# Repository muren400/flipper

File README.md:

# flipper
Currently flipper is just a flip dot clock. display.h could be used for all kinds of flip dot applications though.

## Hardware
Make sure to import https://github.com/espressif/kicad-libraries/ to open the kicad project

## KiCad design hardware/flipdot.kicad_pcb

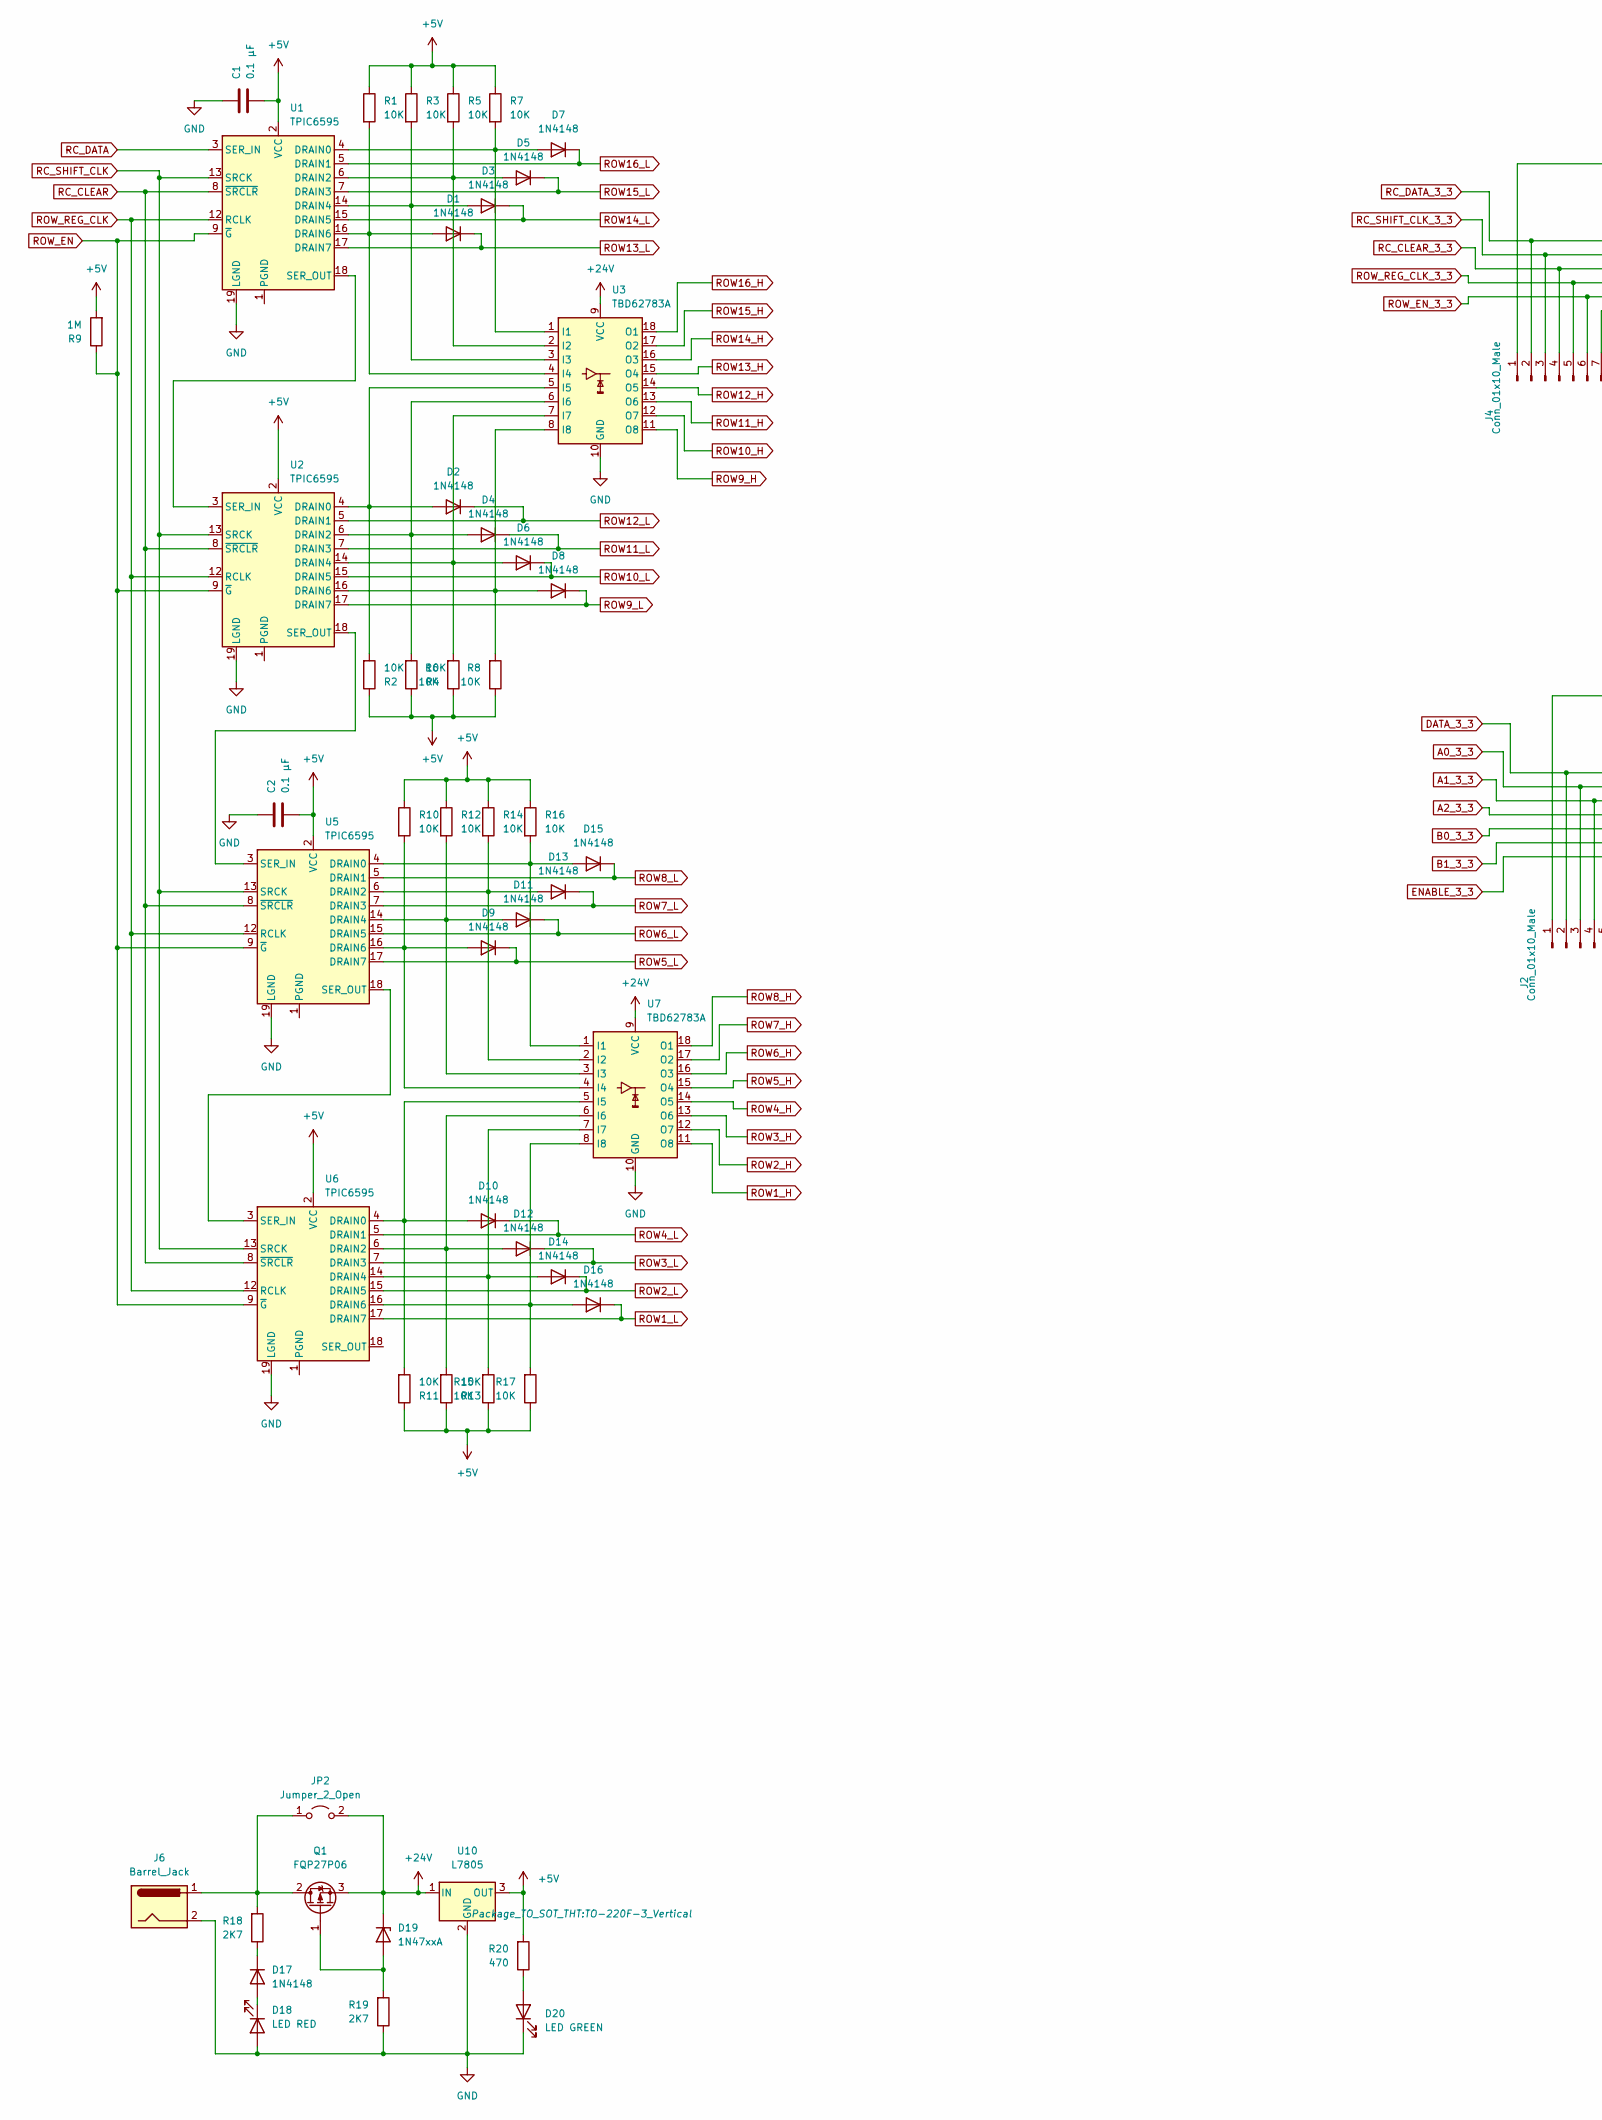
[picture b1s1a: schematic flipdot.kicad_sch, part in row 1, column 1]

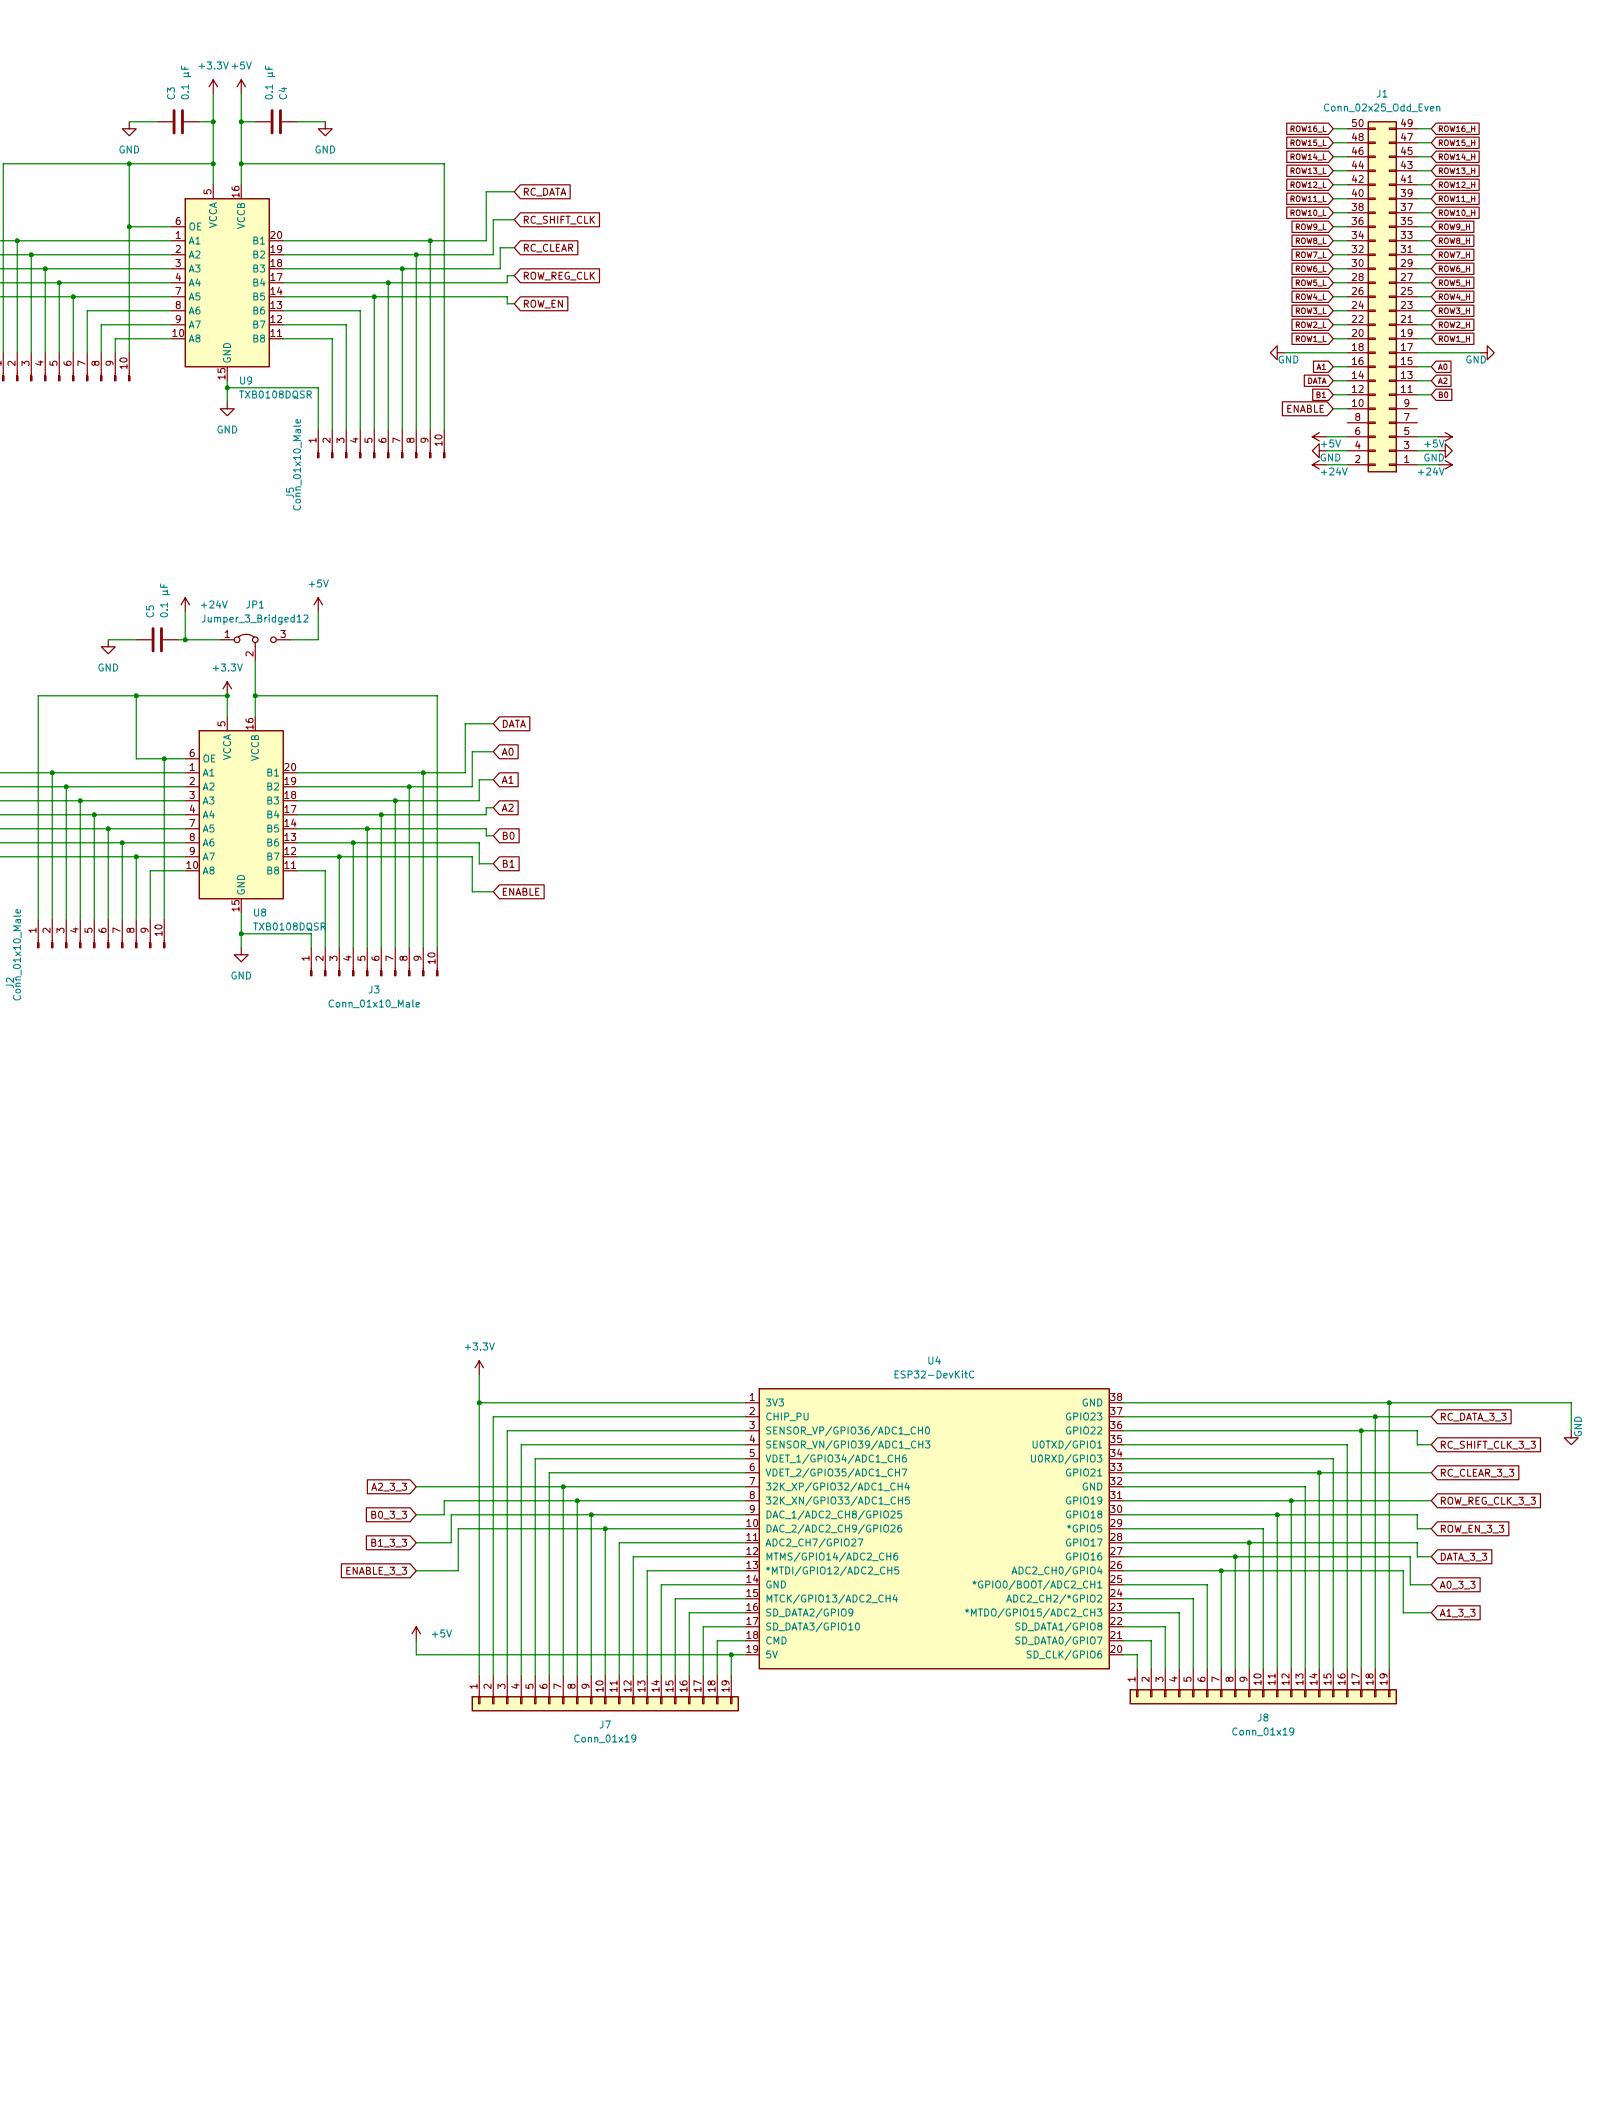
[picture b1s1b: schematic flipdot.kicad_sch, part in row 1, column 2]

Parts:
C1, C2, C3, C4, C5: 0.1 µF; C_Rect_L7.2mm_W2.5mm_P5.00mm_FKS2_FKP2_MKS2_MKP2
D1, D2, D3, D4, D5, D6, D7, D8, D9, D10, D11, D12, D13, D14, D15, D16, D17: 1N4148; D_DO-35_SOD27_P7.62mm_Horizontal
D18: LED RED; LED_D3.0mm
D19: 1N47xxA; D_DO-41_SOD81_P10.16mm_Horizontal
D20: LED GREEN; LED_D3.0mm
J1: Conn_02x25_Odd_Even; PinSocket_2x25_P2.54mm_Vertical
J2, J3, J4, J5: Conn_01x10_Male; PinSocket_1x10_P2.54mm_Vertical
J6: Barrel_Jack; BarrelJack_CUI_PJ-063AH_Horizontal
J7, J8: Conn_01x19; PinHeader_1x19_P2.54mm_Vertical
JP1: Jumper_3_Bridged12; PinHeader_1x03_P2.54mm_Vertical
JP2: Jumper_2_Open; PinHeader_1x02_P2.54mm_Vertical
Q1: FQP27P06; TO-220-3_Vertical
R1, R2, R3, R4, R5, R6, R7, R8, R10, R11, R12, R13, R14, R15, R16, R17: 10K; R_Axial_DIN0204_L3.6mm_D1.6mm_P7.62mm_Horizontal
R9: 1M; R_Axial_DIN0204_L3.6mm_D1.6mm_P7.62mm_Horizontal
R18, R19: 2K7; R_Axial_DIN0204_L3.6mm_D1.6mm_P7.62mm_Horizontal
R20: 470; R_Axial_DIN0204_L3.6mm_D1.6mm_P7.62mm_Horizontal
U1, U2, U5, U6: TPIC6595; DIP-20_W7.62mm_Socket_LongPads
U3, U7: TBD62783A; DIP-18_W7.62mm_Socket_LongPads
U4: ESP32-DevKitC
U8, U9: TXB0108DQSR; USON-20_2x4mm_P0.4mm
U10: L7805; TO-220F-3_Vertical

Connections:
+3.3V: C3.2, J2.1, J2.10, J4.1, J4.10, J7.1, U4.1 (3V3), U8.5 (VCCA), U8.6 (OE), U9.5 (VCCA), U9.6 (OE)
+5V: C1.2, C2.2, C4.2, J1.5, J1.6, J5.10, J7.19, JP1.3 (B), R1.1, R2.1, R3.1, R4.1, R5.1, R6.1, R7.1, R8.1, R9.2, R10.1, R11.1, R12.1, R13.1, R14.1, R15.1, R16.1, R17.1, R20.2, U1.2 (VCC), U2.2 (VCC), U4.19 (5V), U5.2 (VCC), U6.2 (VCC), U9.16 (VCCB), U10.3 (OUT)
+24V: C5.2, D19.1 (K), J1.1, J1.2, JP1.1 (A), JP2.2 (B), Q1.3 (S), U3.9 (VCC), U7.9 (VCC), U10.1 (IN)
A0: J1.15, J3.8, U8.19 (B2)
A0_3_3: J2.3, J8.8, U4.27 (GPIO16), U8.2 (A2)
A1: J1.16, J3.7, U8.18 (B3)
A1_3_3: J2.4, J8.7, U4.26 (ADC2_CH0/GPIO4), U8.3 (A3)
A2: J1.13, J3.6, U8.17 (B4)
A2_3_3: J2.5, J7.7, U4.7 (32K_XP/GPIO32/ADC1_CH4), U8.4 (A4)
B0: J1.11, J3.5, U8.14 (B5)
B0_3_3: J2.6, J7.8, U4.8 (32K_XN/GPIO33/ADC1_CH5), U8.7 (A5)
B1: J1.12, J3.4, U8.13 (B6)
B1_3_3: J2.7, J7.9, U4.9 (DAC_1/ADC2_CH8/GPIO25), U8.8 (A6)
DATA: J1.14, J3.9, U8.20 (B1)
DATA_3_3: J2.2, J8.9, U4.28 (GPIO17), U8.1 (A1)
ENABLE: J1.10, J3.3, U8.12 (B7)
ENABLE_3_3: J2.8, J7.10, U4.10 (DAC_2/ADC2_CH9/GPIO26), U8.9 (A7)
GND: C1.1, C2.1, C3.1, C4.1, C5.1, D18.2 (A), D20.1 (K), J1.3, J1.4, J1.17, J1.18, J3.1, J5.1, J6.2, J8.19, R19.1, U1.19 (LGND), U2.19 (LGND), U3.10 (GND), U4.38 (GND), U5.19 (LGND), U6.19 (LGND), U7.10 (GND), U8.15 (GND), U9.15 (GND), U10.2 (GND)
unnamed: D1.2 (A), R1.2, U1.16 (DRAIN6), U3.4 (I4)
unnamed: D2.2 (A), R2.2, U2.4 (DRAIN0), U3.5 (I5)
unnamed: D3.2 (A), R3.2, U1.14 (DRAIN4), U3.3 (I3)
unnamed: D4.2 (A), R4.2, U2.6 (DRAIN2), U3.6 (I6)
unnamed: D5.2 (A), R5.2, U1.6 (DRAIN2), U3.2 (I2)
unnamed: D6.2 (A), R6.2, U2.14 (DRAIN4), U3.7 (I7)
unnamed: D7.2 (A), R7.2, U1.4 (DRAIN0), U3.1 (I1)
unnamed: D8.2 (A), R8.2, U2.16 (DRAIN6), U3.8 (I8)
unnamed: D9.2 (A), R10.2, U5.16 (DRAIN6), U7.4 (I4)
unnamed: D10.2 (A), R11.2, U6.4 (DRAIN0), U7.5 (I5)
unnamed: D11.2 (A), R12.2, U5.14 (DRAIN4), U7.3 (I3)
unnamed: D12.2 (A), R13.2, U6.6 (DRAIN2), U7.6 (I6)
unnamed: D13.2 (A), R14.2, U5.6 (DRAIN2), U7.2 (I2)
unnamed: D14.2 (A), R15.2, U6.14 (DRAIN4), U7.7 (I7)
unnamed: D15.2 (A), R16.2, U5.4 (DRAIN0), U7.1 (I1)
unnamed: D16.2 (A), R17.2, U6.16 (DRAIN6), U7.8 (I8)
unnamed: D17.2 (A), D18.1 (K)
unnamed: D17.1 (K), R18.1
unnamed: D19.2 (A), Q1.1 (G), R19.2
unnamed: D20.2 (A), R20.1
unnamed: J2.9, U8.10 (A8)
unnamed: J3.2, U8.11 (B8)
unnamed: J3.10, JP1.2 (C), U8.16 (VCCB)
unnamed: J4.7, U9.8 (A6)
unnamed: J4.8, U9.9 (A7)
unnamed: J4.9, U9.10 (A8)
unnamed: J5.2, U9.11 (B8)
unnamed: J5.3, U9.12 (B7)
unnamed: J5.4, U9.13 (B6)
unnamed: J7.2, U4.2 (CHIP_PU)
unnamed: J7.3, U4.3 (SENSOR_VP/GPIO36/ADC1_CH0)
unnamed: J7.4, U4.4 (SENSOR_VN/GPIO39/ADC1_CH3)
unnamed: J7.5, U4.5 (VDET_1/GPIO34/ADC1_CH6)
unnamed: J7.6, U4.6 (VDET_2/GPIO35/ADC1_CH7)
unnamed: J7.11, U4.11 (ADC2_CH7/GPIO27)
unnamed: J7.12, U4.12 (MTMS/GPIO14/ADC2_CH6)
unnamed: J7.13, U4.13 (*MTDI/GPIO12/ADC2_CH5)
unnamed: J7.14, U4.14 (GND)
unnamed: J7.15, U4.15 (MTCK/GPIO13/ADC2_CH4)
unnamed: J7.16, U4.16 (SD_DATA2/GPIO9)
unnamed: J7.17, U4.17 (SD_DATA3/GPIO10)
unnamed: J7.18, U4.18 (CMD)
unnamed: J8.1, U4.20 (SD_CLK/GPIO6)
unnamed: J8.2, U4.21 (SD_DATA0/GPIO7)
unnamed: J8.3, U4.22 (SD_DATA1/GPIO8)
unnamed: J8.4, U4.23 (*MTDO/GPIO15/ADC2_CH3)
unnamed: J8.5, U4.24 (ADC2_CH2/*GPIO2)
unnamed: J8.6, U4.25 (*GPIO0/BOOT/ADC2_CH1)
unnamed: J8.10, U4.29 (*GPIO5)
unnamed: J8.13, U4.32 (GND)
unnamed: J8.15, U4.34 (U0RXD/GPIO3)
unnamed: J8.16, U4.35 (U0TXD/GPIO1)
unnamed: J6.1, JP2.1 (A), Q1.2 (D), R18.2
unnamed: U1.1 (PGND), U1.10 (PGND), U1.11 (PGND), U1.20 (PGND)
unnamed: U1.18 (SER_OUT), U2.3 (SER_IN)
unnamed: U2.1 (PGND), U2.10 (PGND), U2.11 (PGND), U2.20 (PGND)
unnamed: U2.18 (SER_OUT), U5.3 (SER_IN)
unnamed: U5.1 (PGND), U5.10 (PGND), U5.11 (PGND), U5.20 (PGND)
unnamed: U5.18 (SER_OUT), U6.3 (SER_IN)
unnamed: U6.1 (PGND), U6.10 (PGND), U6.11 (PGND), U6.20 (PGND)
RC_CLEAR: J5.7, U1.8 (~SRCLR), U2.8 (~SRCLR), U5.8 (~SRCLR), U6.8 (~SRCLR), U9.18 (B3)
RC_CLEAR_3_3: J4.4, J8.14, U4.33 (GPIO21), U9.3 (A3)
RC_DATA: J5.9, U1.3 (SER_IN), U9.20 (B1)
RC_DATA_3_3: J4.2, J8.18, U4.37 (GPIO23), U9.1 (A1)
RC_SHIFT_CLK: J5.8, U1.13 (SRCK), U2.13 (SRCK), U5.13 (SRCK), U6.13 (SRCK), U9.19 (B2)
RC_SHIFT_CLK_3_3: J4.3, J8.17, U4.36 (GPIO22), U9.2 (A2)
ROW1_H: J1.19, U7.11 (O8)
ROW1_L: D16.1 (K), J1.20, U6.17 (DRAIN7)
ROW2_H: J1.21, U7.12 (O7)
ROW2_L: D14.1 (K), J1.22, U6.15 (DRAIN5)
ROW3_H: J1.23, U7.13 (O6)
ROW3_L: D12.1 (K), J1.24, U6.7 (DRAIN3)
ROW4_H: J1.25, U7.14 (O5)
ROW4_L: D10.1 (K), J1.26, U6.5 (DRAIN1)
ROW5_H: J1.27, U7.15 (O4)
ROW5_L: D9.1 (K), J1.28, U5.17 (DRAIN7)
ROW6_H: J1.29, U7.16 (O3)
ROW6_L: D11.1 (K), J1.30, U5.15 (DRAIN5)
ROW7_H: J1.31, U7.17 (O2)
ROW7_L: D13.1 (K), J1.32, U5.7 (DRAIN3)
ROW8_H: J1.33, U7.18 (O1)
ROW8_L: D15.1 (K), J1.34, U5.5 (DRAIN1)
ROW9_H: J1.35, U3.11 (O8)
ROW9_L: D8.1 (K), J1.36, U2.17 (DRAIN7)
ROW10_H: J1.37, U3.12 (O7)
ROW10_L: D6.1 (K), J1.38, U2.15 (DRAIN5)
ROW11_H: J1.39, U3.13 (O6)
ROW11_L: D4.1 (K), J1.40, U2.7 (DRAIN3)
ROW12_H: J1.41, U3.14 (O5)
ROW12_L: D2.1 (K), J1.42, U2.5 (DRAIN1)
ROW13_H: J1.43, U3.15 (O4)
ROW13_L: D1.1 (K), J1.44, U1.17 (DRAIN7)
ROW14_H: J1.45, U3.16 (O3)
ROW14_L: D3.1 (K), J1.46, U1.15 (DRAIN5)
ROW15_H: J1.47, U3.17 (O2)
ROW15_L: D5.1 (K), J1.48, U1.7 (DRAIN3)
ROW16_H: J1.49, U3.18 (O1)
ROW16_L: D7.1 (K), J1.50, U1.5 (DRAIN1)
ROW_EN: J5.5, R9.1, U1.9 (~G), U2.9 (~G), U5.9 (~G), U6.9 (~G), U9.14 (B5)
ROW_EN_3_3: J4.6, J8.11, U4.30 (GPIO18), U9.7 (A5)
ROW_REG_CLK: J5.6, U1.12 (RCLK), U2.12 (RCLK), U5.12 (RCLK), U6.12 (RCLK), U9.17 (B4)
ROW_REG_CLK_3_3: J4.5, J8.12, U4.31 (GPIO19), U9.4 (A4)

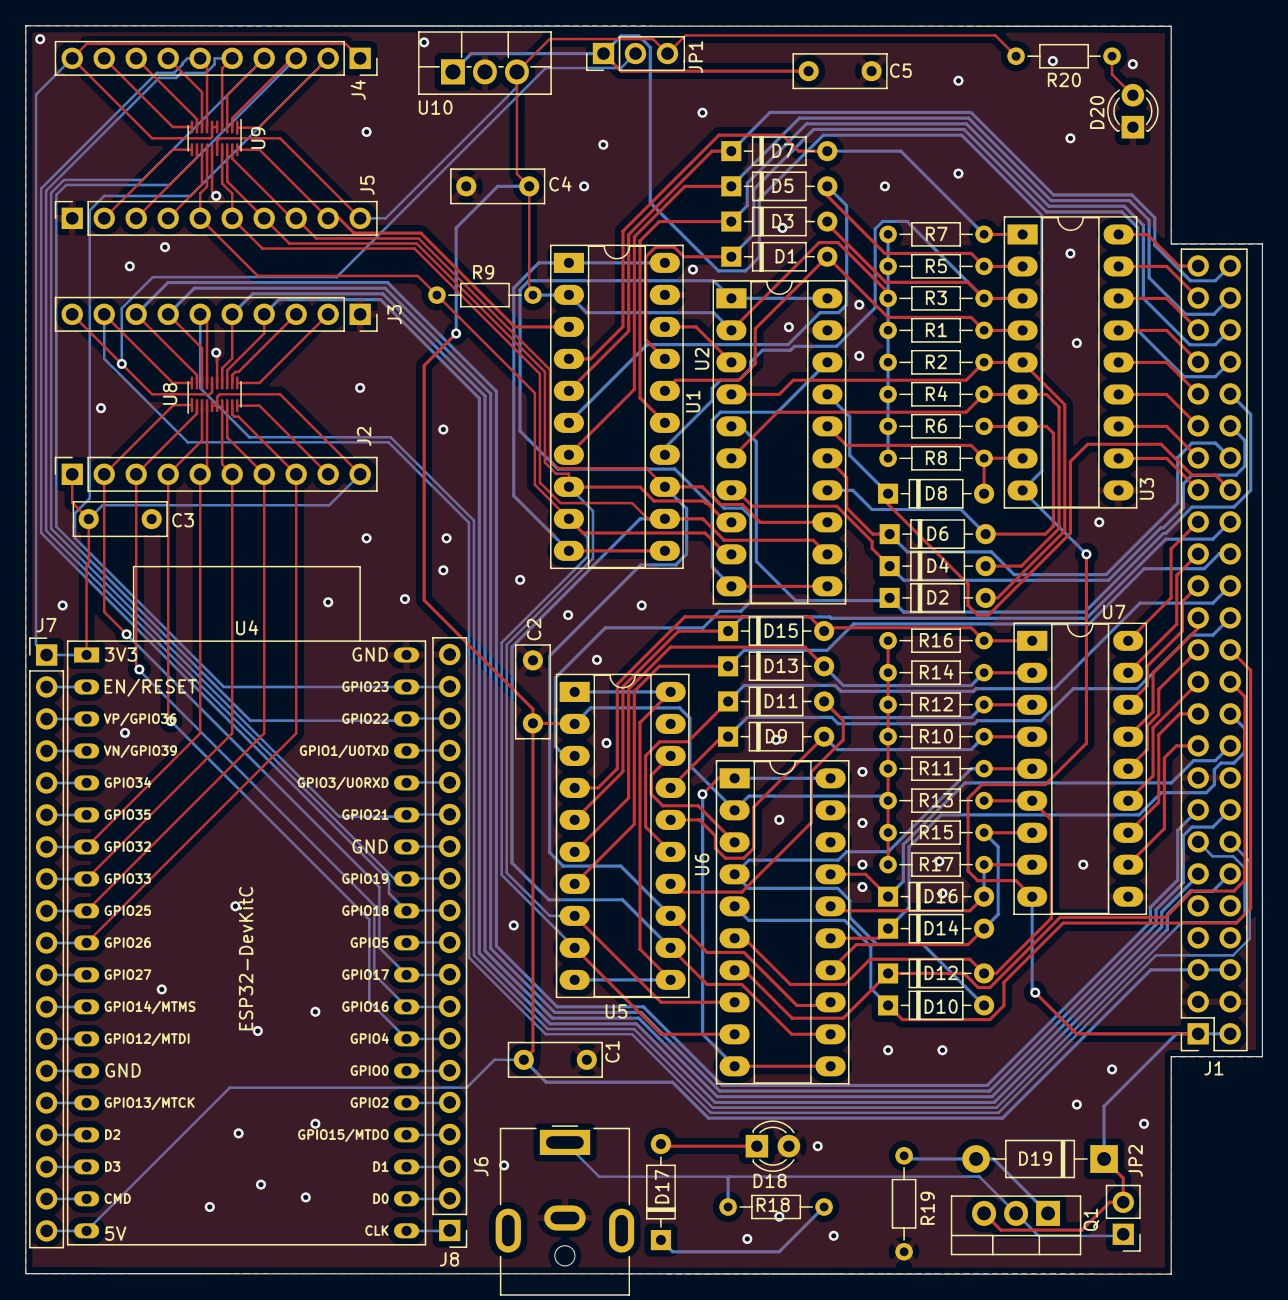
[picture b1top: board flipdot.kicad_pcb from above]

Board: 2 copper layers, 98.2 x 99.1 mm, 66 parts (0 on the bottom side), 120 nets.

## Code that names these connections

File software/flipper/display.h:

// #include "esp32-hal.h"
#ifndef DISPLAY_H
#define DISPLAY_H

#include "characters.h"
#include "flipper.h"

#define LATCH_PIN 19  // ROW_REG_CLK
#define CLOCK_PIN 22  // RC_SHIFT_CLK
#define DATA_PIN 23   // RC_DATA

#define CLEAR 21
#define ROW_EN 18

#define COL_DATA_PIN 17
#define COL_EN 26

#define A_0 16
#define A_1 4
#define A_2 32
#define B_0 33
#define B_1 25

class Display {
 public:
  Display() { init(); }

  void clearPixelBuffer() {
    for (int i = 0; i < 16; i++) {
      pixelBuffer[i] = 0;
    }
  }

  void setUpdateTime(uint32_t value) {
    updateTimeInMillis = value;
  }

  // maxY = 9
  void drawCharacter(uint8_t x, uint8_t y, char character) {
    x = 24 - x;

    for (int i = 0; i < 11; i++) {
      pixelBuffer[i + y] |= (uint32_t)((characters[i + (character * 11)]) << x);
    }
  }

  void drawPixel(uint8_t x, uint8_t y) {}

  void writePixelBuffer() {
    static bool isInitialWrite = true;

    for (int i = 0; i < 16; i++) {
      for (int j = 0; j < 28; j++) {
        uint32_t bitMask = (1 << 27) >> j;
        uint32_t maskedPixel = pixelBuffer[i] & bitMask;
        uint32_t oldMaskedPixel = oldPixelBuffer[i] & bitMask;

        bool pixelHasNotChanged = oldMaskedPixel == maskedPixel;
        if (pixelHasNotChanged && !isInitialWrite) {
          continue;
        }

        bool isOn = maskedPixel > 0;
        setPixel(i, j, isOn);
      }

      oldPixelBuffer[i] = pixelBuffer[i];
    }
    
    isInitialWrite = false;
  }

 private:
  bool dirty = true;

  uint32_t updateTimeInMillis = 20;

  uint8_t rowBuffer[4];
  uint32_t pixelBuffer[16];
  uint32_t oldPixelBuffer[16];

  void init() {
    pinMode(LATCH_PIN, OUTPUT);
    pinMode(CLOCK_PIN, OUTPUT);
    pinMode(DATA_PIN, OUTPUT);
    pinMode(ROW_EN, OUTPUT);
    pinMode(CLEAR, OUTPUT);

    pinMode(COL_EN, OUTPUT);
    pinMode(COL_DATA_PIN, OUTPUT);
    pinMode(A_0, OUTPUT);
    pinMode(A_1, OUTPUT);
    pinMode(A_2, OUTPUT);
    pinMode(B_0, OUTPUT);
    pinMode(B_1, OUTPUT);

    digitalWrite(ROW_EN, LOW);
    digitalWrite(CLEAR, LOW);
    digitalWrite(CLEAR, HIGH);
    digitalWrite(LATCH_PIN, LOW);
    digitalWrite(CLOCK_PIN, LOW);

    digitalWrite(COL_EN, LOW);
    digitalWrite(COL_DATA_PIN, LOW);
    digitalWrite(A_0, LOW);
    digitalWrite(A_1, LOW);
    digitalWrite(A_2, LOW);
    digitalWrite(B_0, LOW);
    digitalWrite(B_1, LOW);

    setNeutral();
    // fillDisplay();
    clearDisplay();
    setNeutral();
  }

  void setRowHigh(uint8_t row) {
    for (int i = 0; i < 4; i++) {
      uint8_t value = 0;

      for (int j = 0; j < 8; j += 2) {
        value |= (1 << j);
      }

      if (row / 4 == i) {
        uint8_t bitIndex = (row % 4) * 2;
        value &= ~(1 << bitIndex);
      }

      rowBuffer[i] = value;
    }

    writeRowBuffer();
  }

  // 1 1
  void setRowLow(uint8_t row) {
    for (int i = 0; i < 4; i++) {
      uint8_t value = 0;

      for (int j = 0; j < 8; j += 2) {
        value |= (1 << j);
      }

      if (row / 4 == i) {
        uint8_t bitIndex = ((row % 4) * 2) + 1;
        value |= (1 << bitIndex);
      }

      rowBuffer[i] = value;
    }

    writeRowBuffer();
  }

  void setNeutral() {
    rowBuffer[0] = 0b01010101;
    rowBuffer[1] = 0b01010101;
    rowBuffer[2] = 0b01010101;
    rowBuffer[3] = 0b01010101;
    writeRowBuffer();
  }

  // B1 B0 A2 A1 A0
  //  0  0  0  0  1 => 0
  //  1  1  1  1  1 => 28
  void setColumnAdress(uint8_t col) {
    col++;

    if (col > 7) {
      col++;
    }

    if (col > 15) {
      col++;
    }

    if (col > 23) {
      col++;
    }

    setColumnBit(col, 0, A_0);
    setColumnBit(col, 1, A_1);
    setColumnBit(col, 2, A_2);
    setColumnBit(col, 3, B_0);
    setColumnBit(col, 4, B_1);
  }

  void setColumnBit(uint8_t col, uint8_t bit, int pin) {
    if ((col & (1 << bit)) > 0) {
      digitalWrite(pin, HIGH);
    } else {
      digitalWrite(pin, LOW);
    }
  }

  void myShiftOut(uint8_t dataPin, uint8_t clockPin, uint8_t bitOrder,
                  uint8_t val) {
    uint8_t i;

    for (i = 0; i < 8; i++) {
      if (bitOrder == LSBFIRST)
        digitalWrite(dataPin, !!(val & (1 << i)));
      else
        digitalWrite(dataPin, !!(val & (1 << (7 - i))));

      digitalWrite(clockPin, HIGH);
      digitalWrite(clockPin, LOW);
    }
  }

  void writeShiftRegisters(uint8_t val) {
    digitalWrite(LATCH_PIN, LOW);
    myShiftOut(DATA_PIN, CLOCK_PIN, LSBFIRST, val);
    digitalWrite(LATCH_PIN, HIGH);
    digitalWrite(LATCH_PIN, LOW);
  }

  void writeRowBuffer() {
    digitalWrite(LATCH_PIN, LOW);
    myShiftOut(DATA_PIN, CLOCK_PIN, MSBFIRST, rowBuffer[3]);
    myShiftOut(DATA_PIN, CLOCK_PIN, MSBFIRST, rowBuffer[2]);
    myShiftOut(DATA_PIN, CLOCK_PIN, MSBFIRST, rowBuffer[1]);
    myShiftOut(DATA_PIN, CLOCK_PIN, MSBFIRST, rowBuffer[0]);
    digitalWrite(LATCH_PIN, HIGH);
    digitalWrite(LATCH_PIN, LOW);
  }

  void enableChip(bool enable) {
    if (enable) {
      digitalWrite(ROW_EN, LOW);
    } else {
      digitalWrite(ROW_EN, HIGH);
    }
  }

  void clearDisplay() {
    for (int j = 0; j < 28; j++) {
      for (int i = 0; i < 16; i++) {
        setPixel(i, j, false);
      }
    }
  }

  void fillDisplay() {
    for (int j = 0; j < 28; j++) {
      for (int i = 0; i < 16; i++) {
        setPixel(i, j, true);
      }
    }
  }

  void setPixel(uint8_t row, uint8_t col, bool isOn) {
    setColumnAdress(col);

    if (isOn) {
      digitalWrite(COL_DATA_PIN, LOW);
      setRowHigh(row);
    } else {
      digitalWrite(COL_DATA_PIN, HIGH);
      setRowLow(row);
    }

    digitalWrite(COL_EN, HIGH);
    delayMicroseconds(500);
    digitalWrite(COL_EN, LOW);
    setNeutral();
    delay(updateTimeInMillis);
  }
};

#endif

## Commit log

2023-06-14 initial comit
2024-01-17 use system time
